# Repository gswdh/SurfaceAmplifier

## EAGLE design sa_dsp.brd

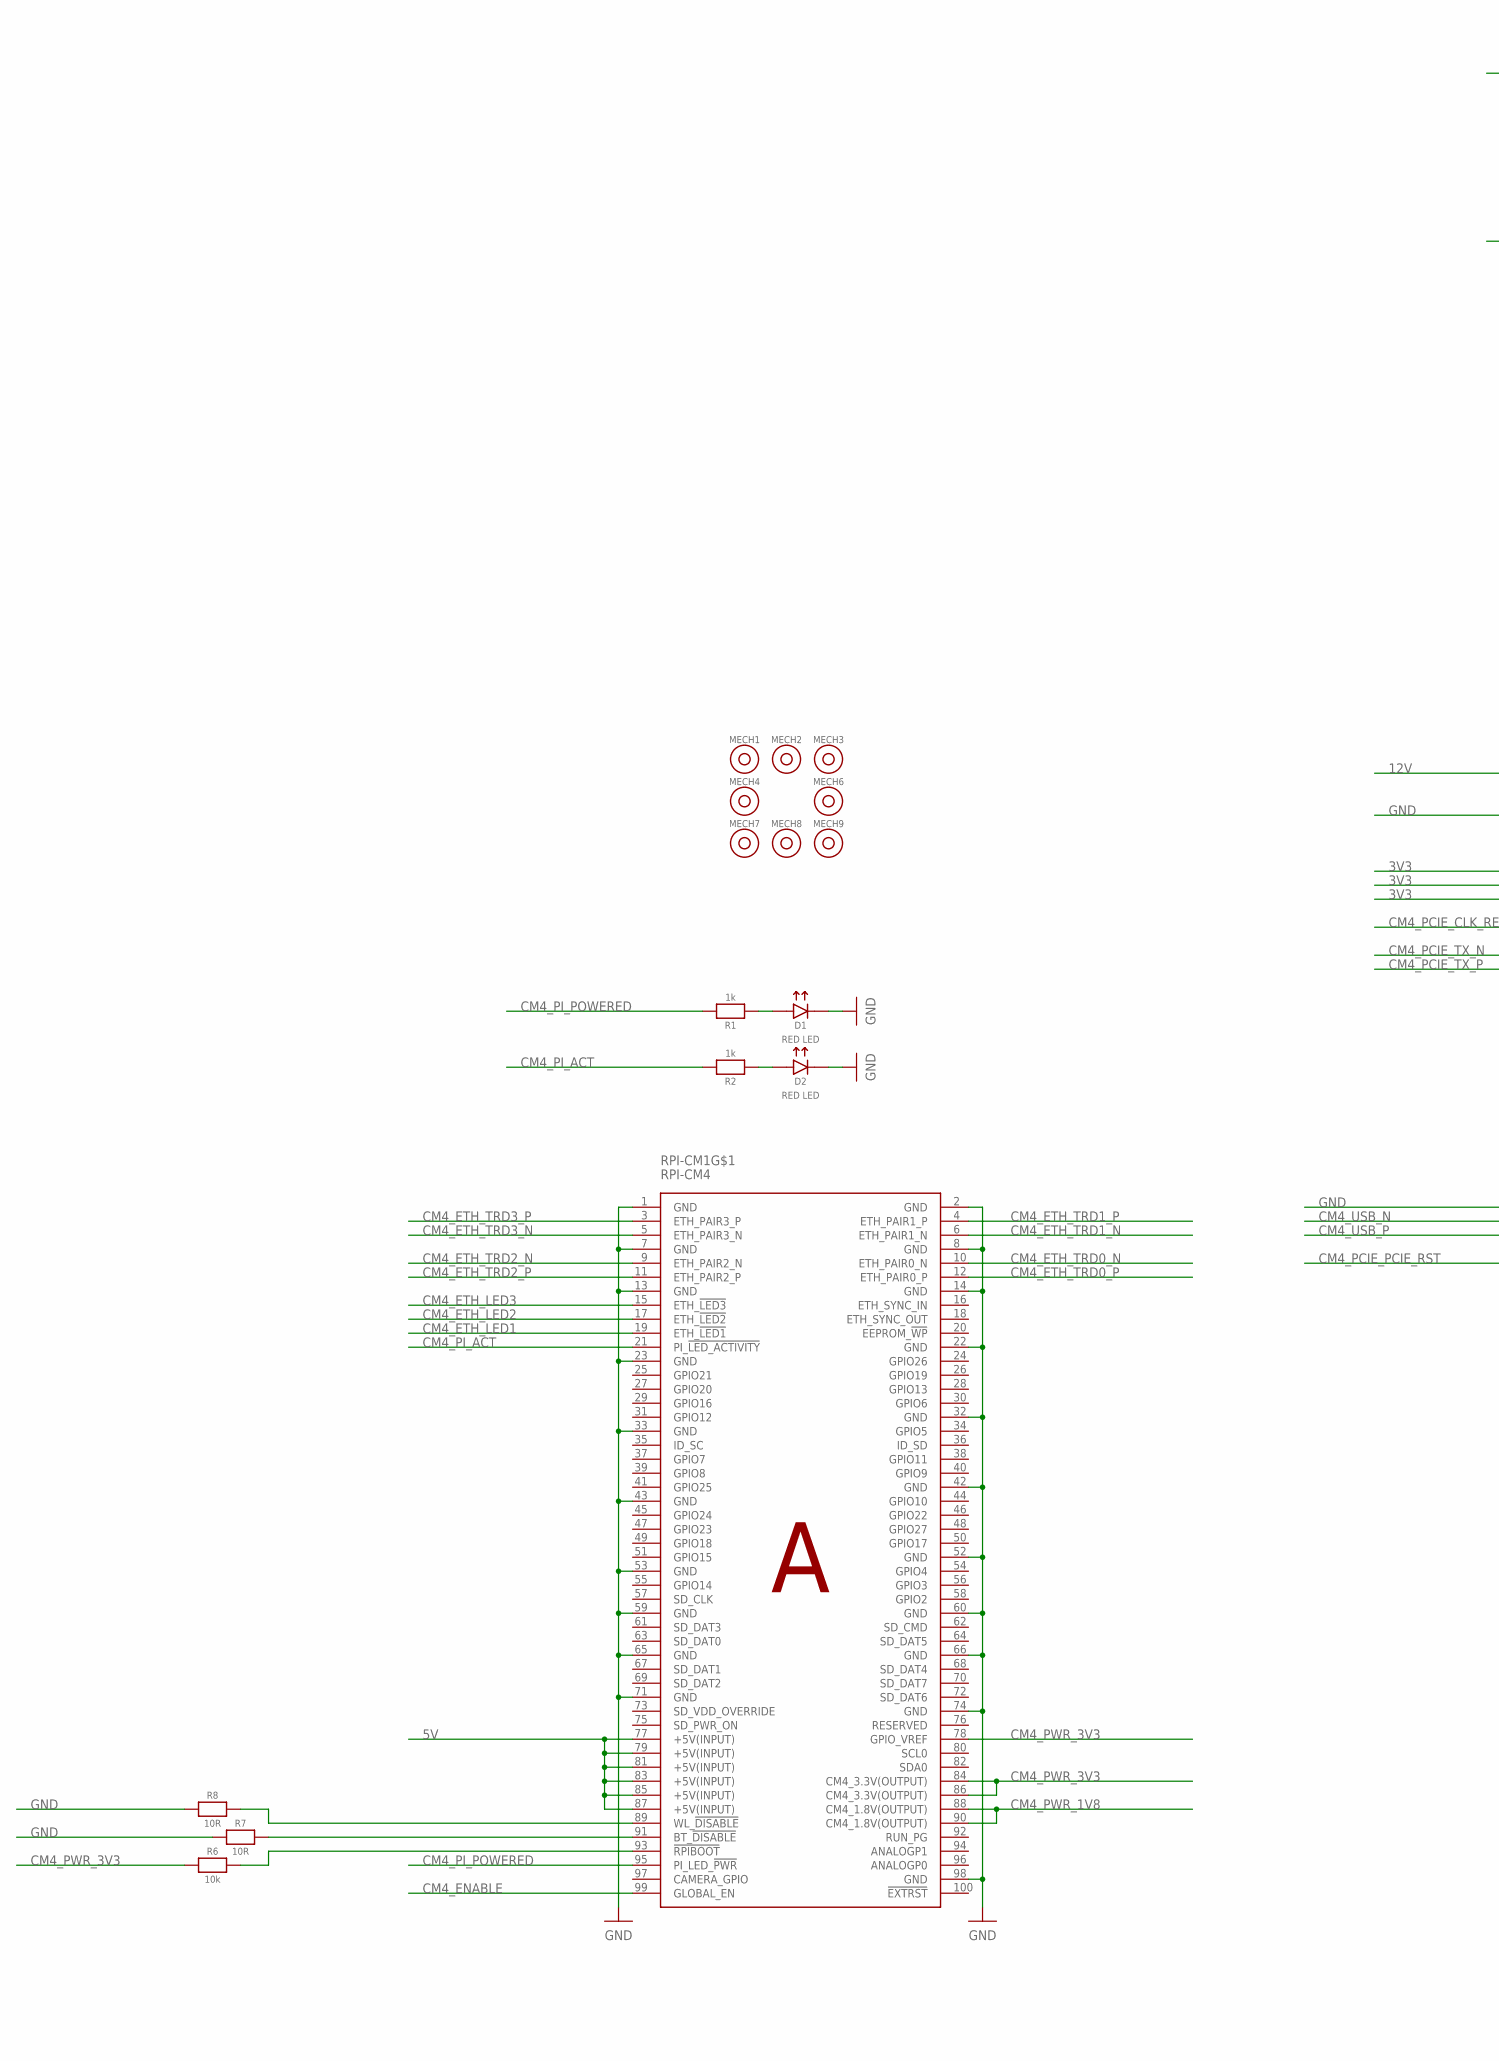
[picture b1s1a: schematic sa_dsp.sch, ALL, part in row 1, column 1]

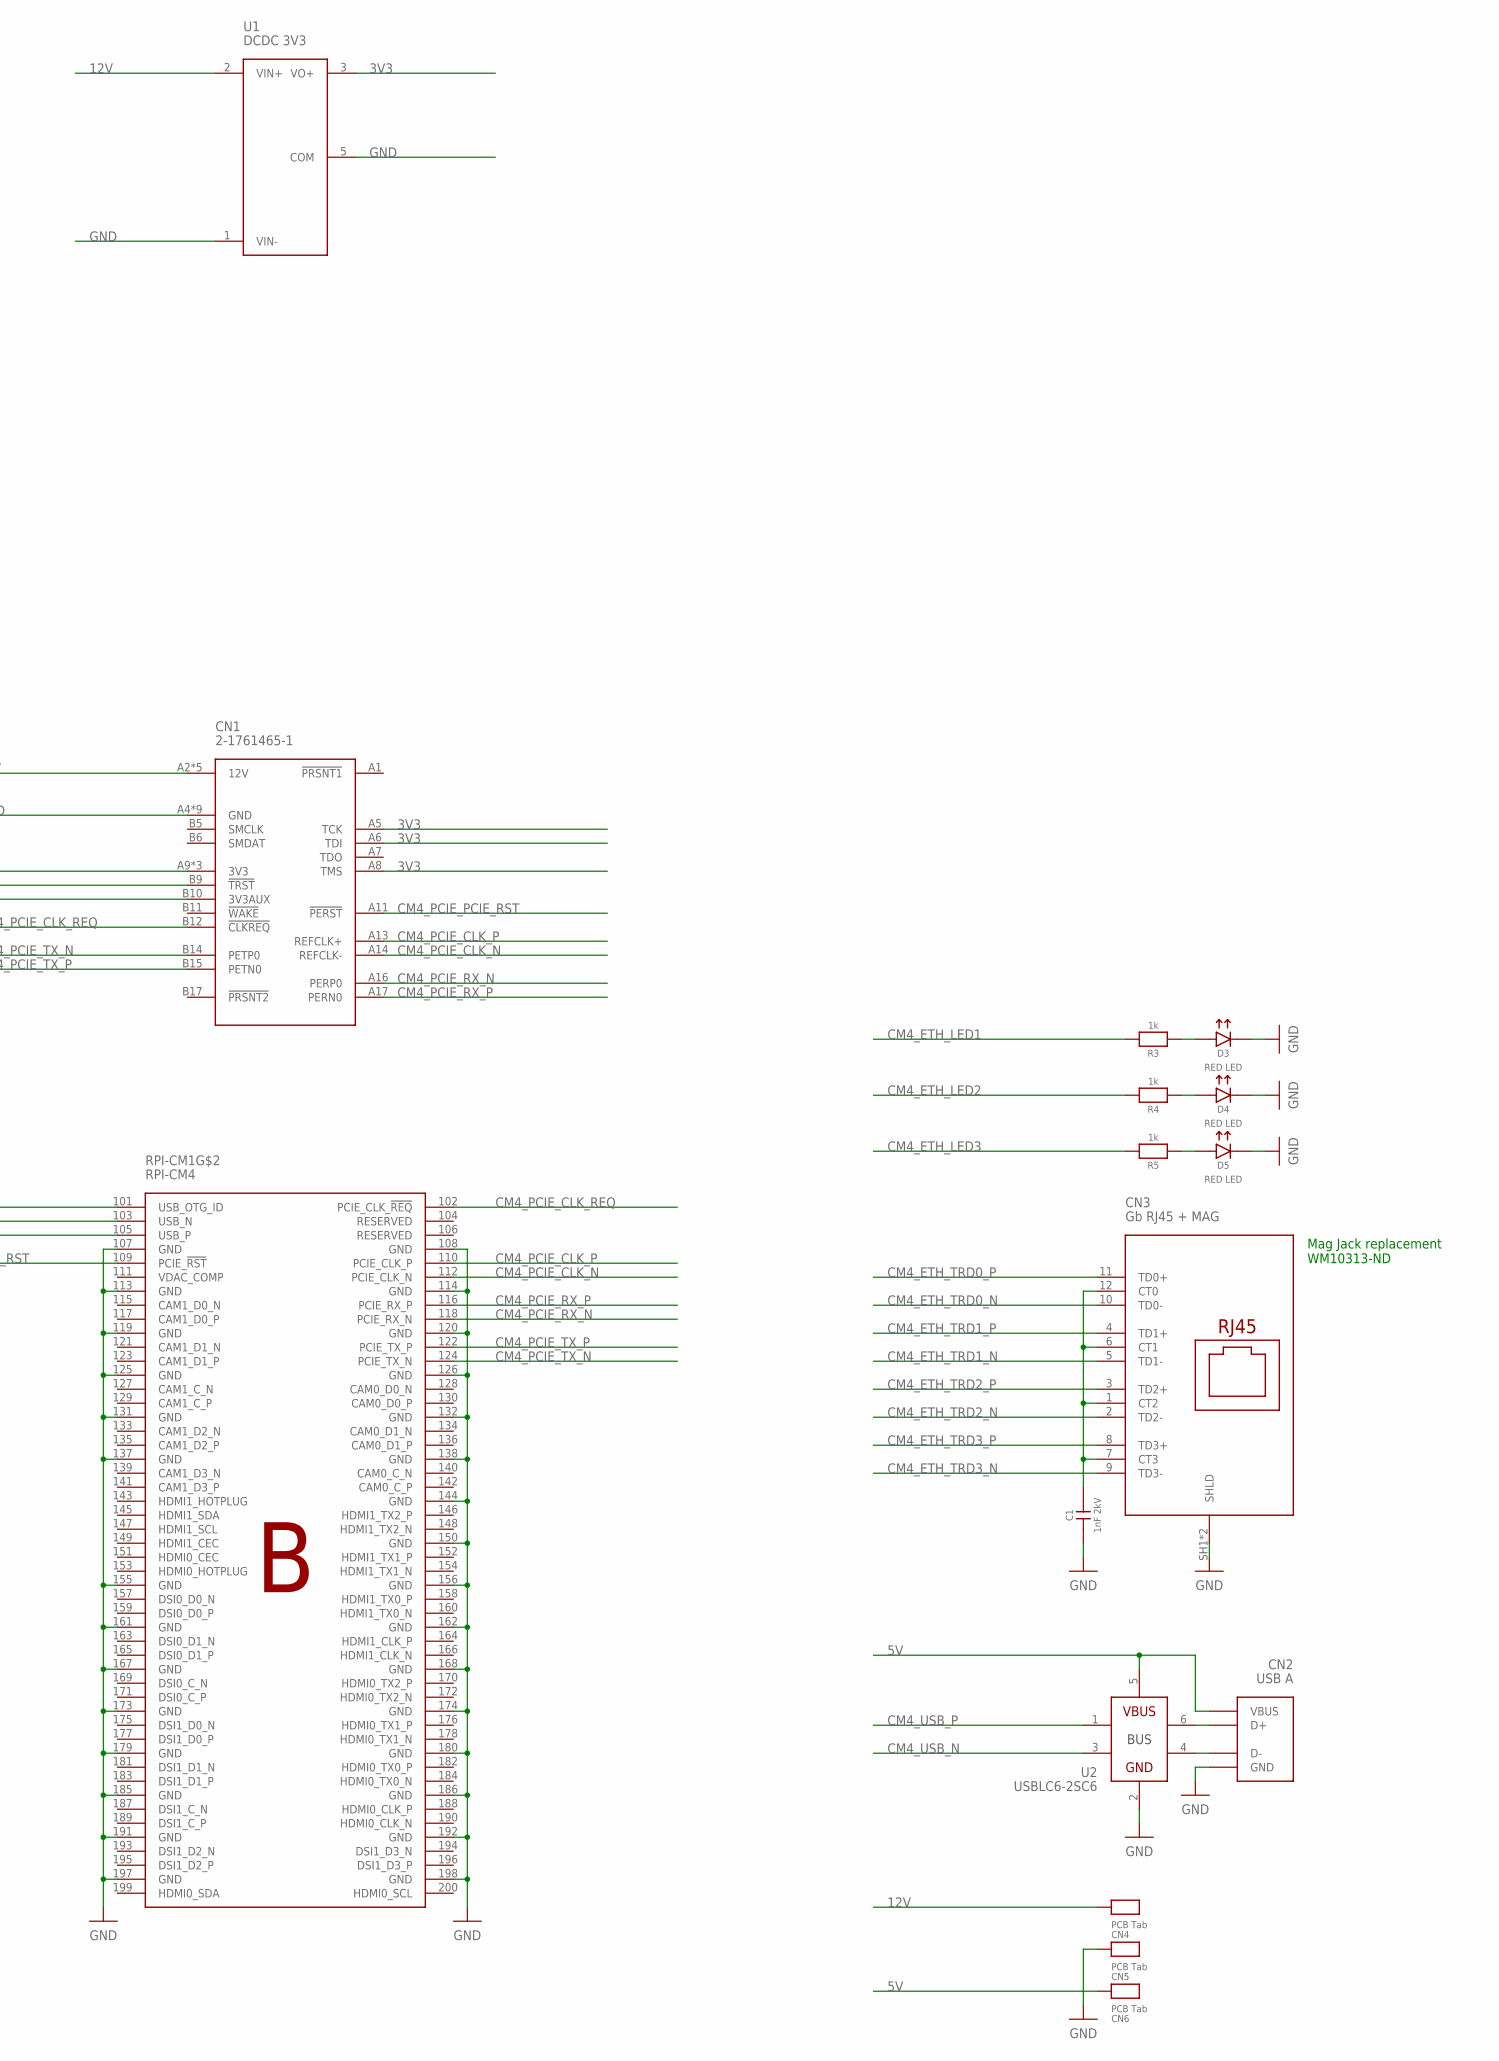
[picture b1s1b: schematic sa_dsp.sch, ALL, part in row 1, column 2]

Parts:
C1: 1nF 2kV; 1812
CN1: 2-1761465-1; CONN36_2-1761465-1_TEC
CN2: USB A; 629104190121
CN3: Gb RJ45 + MAG; 0857931020
CN4, CN5, CN6: PCB Tab; PCB_TAB_SMALL
D1, D2, D3, D4, D5: RED LED; 0603_POLAR
MECH1, MECH2, MECH3, MECH4, MECH6, MECH7, MECH8, MECH9: 6mm x 3mm; MOUNTHOLE_6X3
R1, R2, R3, R4, R5: 1k; 0603
R6: 10k; 0603
R7, R8: 10R; 0603
RPI-CM1: RPI-CM4
U1: DCDC 3V3; PDQE10
U2: USBLC6-2SC6; SOT23-6

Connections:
3V3: CN1.A5 (TCK), CN1.A6 (TDI), CN1.A8 (TMS), CN1.A9 (3V3), CN1.A10 (3V3), CN1.B8 (3V3), CN1.B9 (!TRST), CN1.B10 (3V3AUX), U1.3 (VO+)
5V: CN2.1 (VBUS), CN6.1, RPI-CM1.77 (+5V(INPUT)), RPI-CM1.79 (+5V(INPUT)), RPI-CM1.81 (+5V(INPUT)), RPI-CM1.83 (+5V(INPUT)), RPI-CM1.85 (+5V(INPUT)), RPI-CM1.87 (+5V(INPUT)), U2.5 (VBUS)
12V: CN1.A2 (12V), CN1.A3 (12V), CN1.B1 (12V), CN1.B2 (12V), CN1.B3 (12V), CN4.1, U1.2 (VIN+)
CM4_ENABLE: RPI-CM1.99 (GLOBAL_EN)
CM4_ETH_LED1: R3.2, RPI-CM1.19 (ETH_!LED1)
CM4_ETH_LED2: R4.2, RPI-CM1.17 (ETH_!LED2)
CM4_ETH_LED3: R5.2, RPI-CM1.15 (ETH_!LED3)
CM4_ETH_TRD0_N: CN3.10 (TD0-), RPI-CM1.10 (ETH_PAIR0_N)
CM4_ETH_TRD0_P: CN3.11 (TD0+), RPI-CM1.12 (ETH_PAIR0_P)
CM4_ETH_TRD1_N: CN3.5 (TD1-), RPI-CM1.6 (ETH_PAIR1_N)
CM4_ETH_TRD1_P: CN3.4 (TD1+), RPI-CM1.4 (ETH_PAIR1_P)
CM4_ETH_TRD2_N: CN3.2 (TD2-), RPI-CM1.9 (ETH_PAIR2_N)
CM4_ETH_TRD2_P: CN3.3 (TD2+), RPI-CM1.11 (ETH_PAIR2_P)
CM4_ETH_TRD3_N: CN3.9 (TD3-), RPI-CM1.5 (ETH_PAIR3_N)
CM4_ETH_TRD3_P: CN3.8 (TD3+), RPI-CM1.3 (ETH_PAIR3_P)
CM4_PCIE_CLK_N: CN1.A14 (REFCLK-), RPI-CM1.112 (PCIE_CLK_N)
CM4_PCIE_CLK_P: CN1.A13 (REFCLK+), RPI-CM1.110 (PCIE_CLK_P)
CM4_PCIE_CLK_REQ: CN1.B12 (!CLKREQ), RPI-CM1.102 (PCIE_CLK_!REQ)
CM4_PCIE_PCIE_RST: CN1.A11 (!PERST), RPI-CM1.109 (PCIE_!RST)
CM4_PCIE_RX_N: CN1.A16 (PERP0), RPI-CM1.118 (PCIE_RX_N)
CM4_PCIE_RX_P: CN1.A17 (PERN0), RPI-CM1.116 (PCIE_RX_P)
CM4_PCIE_TX_N: CN1.B14 (PETP0), RPI-CM1.124 (PCIE_TX_N)
CM4_PCIE_TX_P: CN1.B15 (PETN0), RPI-CM1.122 (PCIE_TX_P)
CM4_PI_ACT: R2.2, RPI-CM1.21 (PI_!LED_ACTIVITY)
CM4_PI_POWERED: R1.2, RPI-CM1.95 (PI_LED_!PWR)
CM4_PWR_1V8: RPI-CM1.88 (CM4_1.8V(OUTPUT)), RPI-CM1.90 (CM4_1.8V(OUTPUT))
CM4_PWR_3V3: R6.1, RPI-CM1.78 (GPIO_VREF), RPI-CM1.84 (CM4_3.3V(OUTPUT)), RPI-CM1.86 (CM4_3.3V(OUTPUT))
CM4_USB_N: RPI-CM1.103 (USB_N), U2.3 (D-_IN)
CM4_USB_P: RPI-CM1.105 (USB_P), U2.1 (D+_IN)
GND: C1.1, CN1.A4 (GND), CN1.A12 (GND), CN1.A15 (GND), CN1.A18 (GND), CN1.B4 (GND), CN1.B7 (GND), CN1.B13 (GND), CN1.B16 (GND), CN1.B18 (GND), CN2.4 (GND), CN2.SH1 (GND), CN2.SH2 (GND), CN2.SH3 (GND), CN2.SH4 (GND), CN3.SH1 (SHLD), CN3.SH2 (SHLD), CN5.1, D1.K, D2.K, D3.K, D4.K, D5.K, R7.1, R8.1, RPI-CM1.1 (GND), RPI-CM1.2 (GND), RPI-CM1.7 (GND), RPI-CM1.8 (GND), RPI-CM1.13 (GND), RPI-CM1.14 (GND), RPI-CM1.22 (GND), RPI-CM1.23 (GND), RPI-CM1.32 (GND), RPI-CM1.33 (GND), RPI-CM1.42 (GND), RPI-CM1.43 (GND), RPI-CM1.52 (GND), RPI-CM1.53 (GND), RPI-CM1.59 (GND), RPI-CM1.60 (GND), RPI-CM1.65 (GND), RPI-CM1.66 (GND), RPI-CM1.71 (GND), RPI-CM1.74 (GND), RPI-CM1.98 (GND), RPI-CM1.101 (USB_OTG_ID), RPI-CM1.107 (GND), RPI-CM1.108 (GND), RPI-CM1.113 (GND), RPI-CM1.114 (GND), RPI-CM1.119 (GND), RPI-CM1.120 (GND), RPI-CM1.125 (GND), RPI-CM1.126 (GND), RPI-CM1.131 (GND), RPI-CM1.132 (GND), RPI-CM1.137 (GND), RPI-CM1.138 (GND), RPI-CM1.144 (GND), RPI-CM1.150 (GND), RPI-CM1.155 (GND), RPI-CM1.156 (GND), RPI-CM1.161 (GND), RPI-CM1.162 (GND), RPI-CM1.167 (GND), RPI-CM1.168 (GND), RPI-CM1.173 (GND), RPI-CM1.174 (GND), RPI-CM1.179 (GND), RPI-CM1.180 (GND), RPI-CM1.185 (GND), RPI-CM1.186 (GND), RPI-CM1.191 (GND), RPI-CM1.192 (GND), RPI-CM1.197 (GND), RPI-CM1.198 (GND), U1.1 (VIN-), U1.5 (COM), U2.2 (GND)
unnamed: D1.A, R1.1
unnamed: CN2.2 (D-), U2.4 (D-OUT)
unnamed: D2.A, R2.1
unnamed: CN2.3 (D+), U2.6 (D+_OUT)
unnamed: D3.A, R3.1
unnamed: C1.2, CN3.1 (CT2), CN3.6 (CT1), CN3.7 (CT3), CN3.12 (CT0)
unnamed: D4.A, R4.1
unnamed: R6.2, RPI-CM1.93 (!RPIBOOT)
unnamed: D5.A, R5.1
unnamed: R7.2, RPI-CM1.91 (BT_!DISABLE)
unnamed: R8.2, RPI-CM1.89 (WL_!DISABLE)

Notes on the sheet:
Mag Jack replacement WM10313-ND

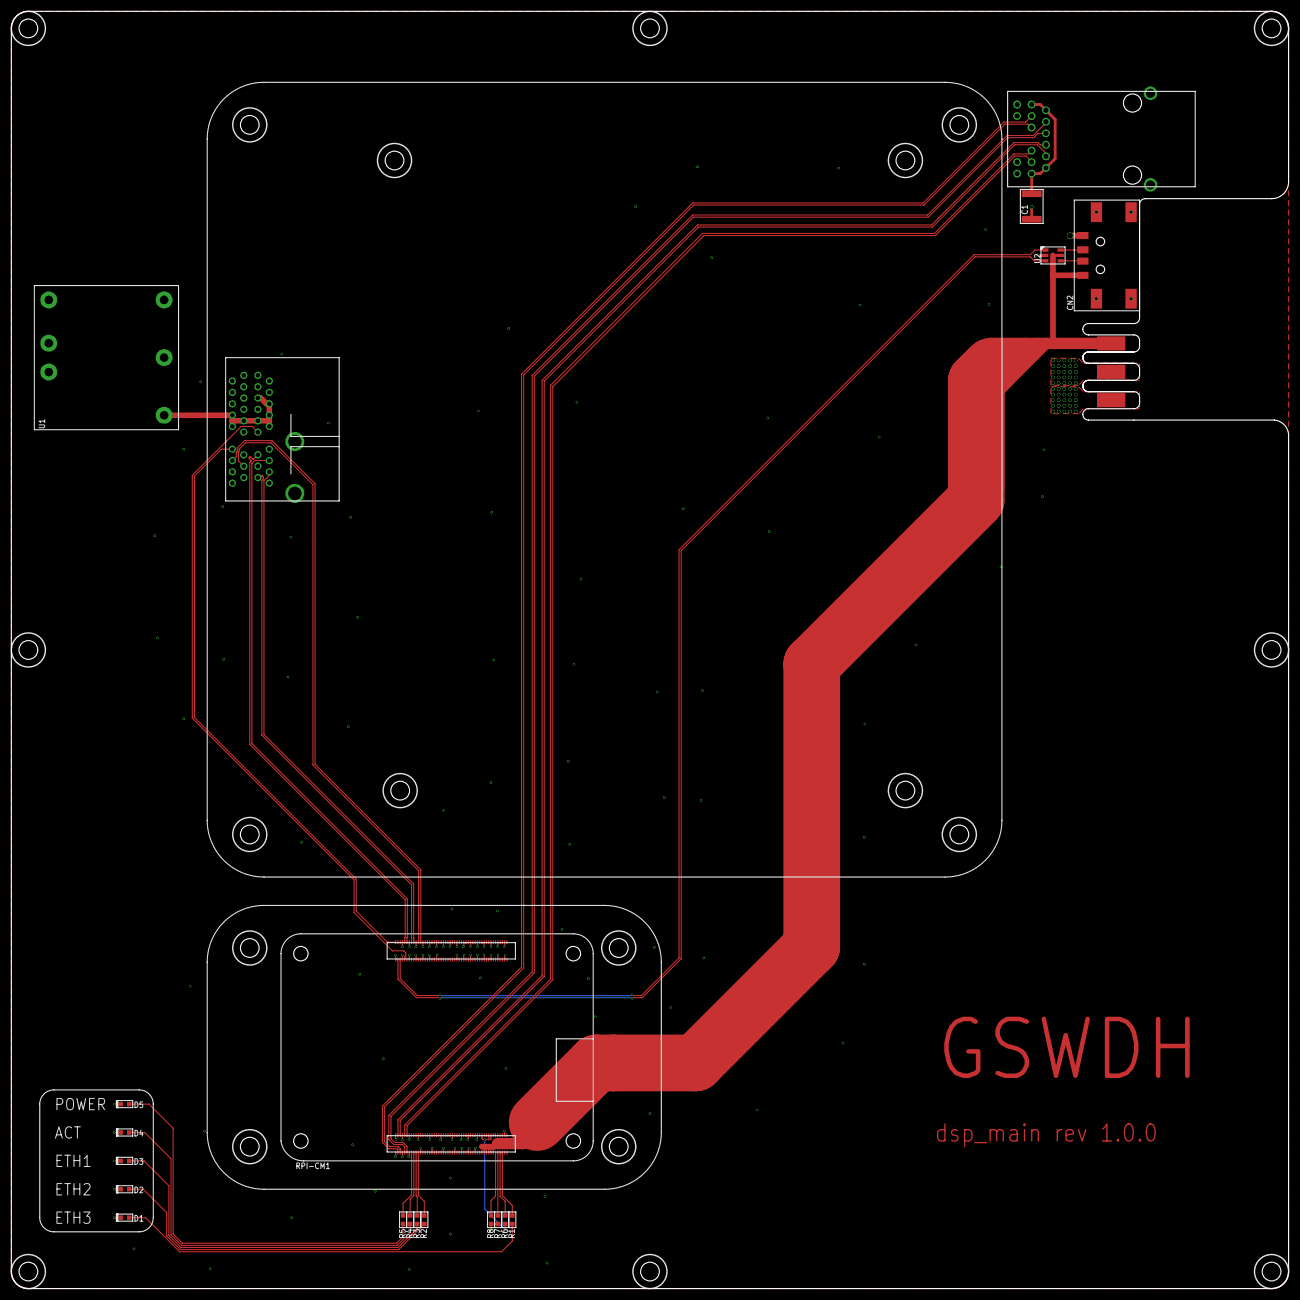
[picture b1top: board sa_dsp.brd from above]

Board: 4 copper layers, 225.0 x 225.0 mm, 43 parts (0 on the bottom side), 40 nets.

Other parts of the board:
MECH5, MECH10, MECH11, MECH12, MECH13, MECH14, MECH15, MECH16, MECH17, MECH18, MECH19, MECH20: 6mm x 3mm; MOUNTHOLE_6X3

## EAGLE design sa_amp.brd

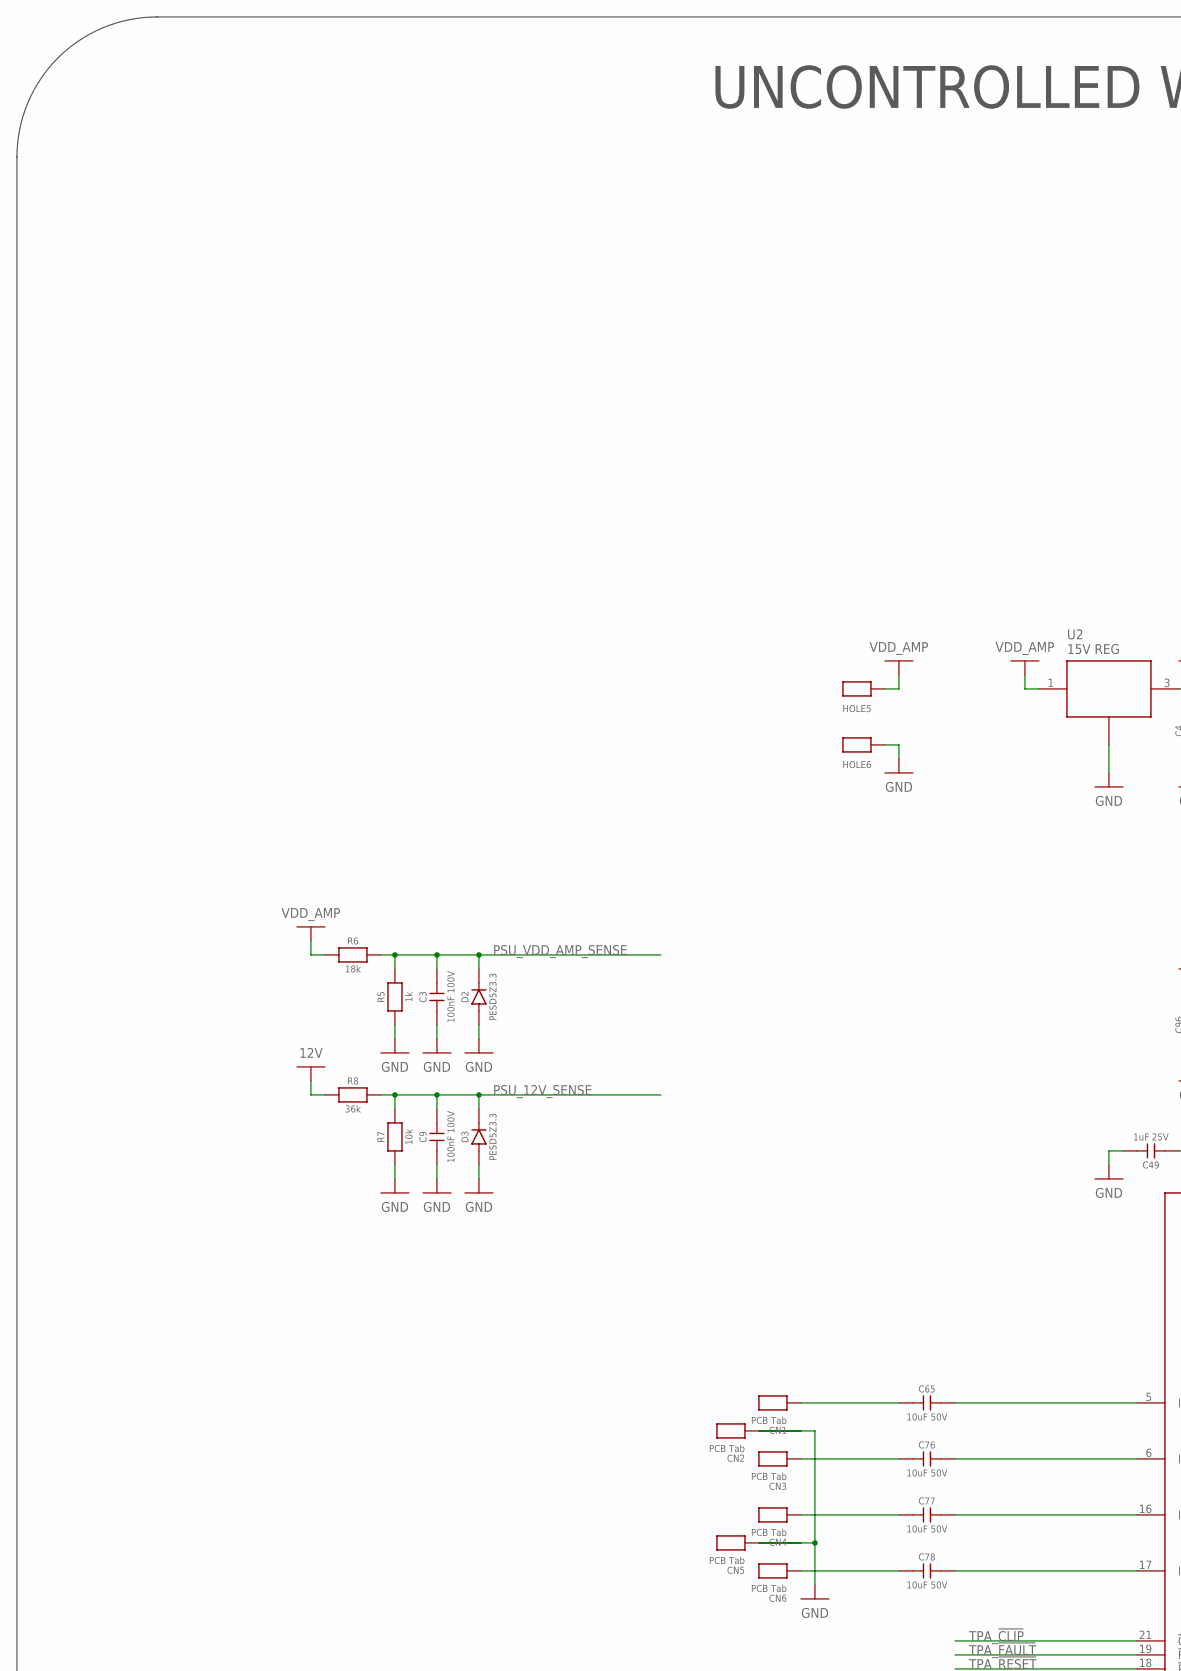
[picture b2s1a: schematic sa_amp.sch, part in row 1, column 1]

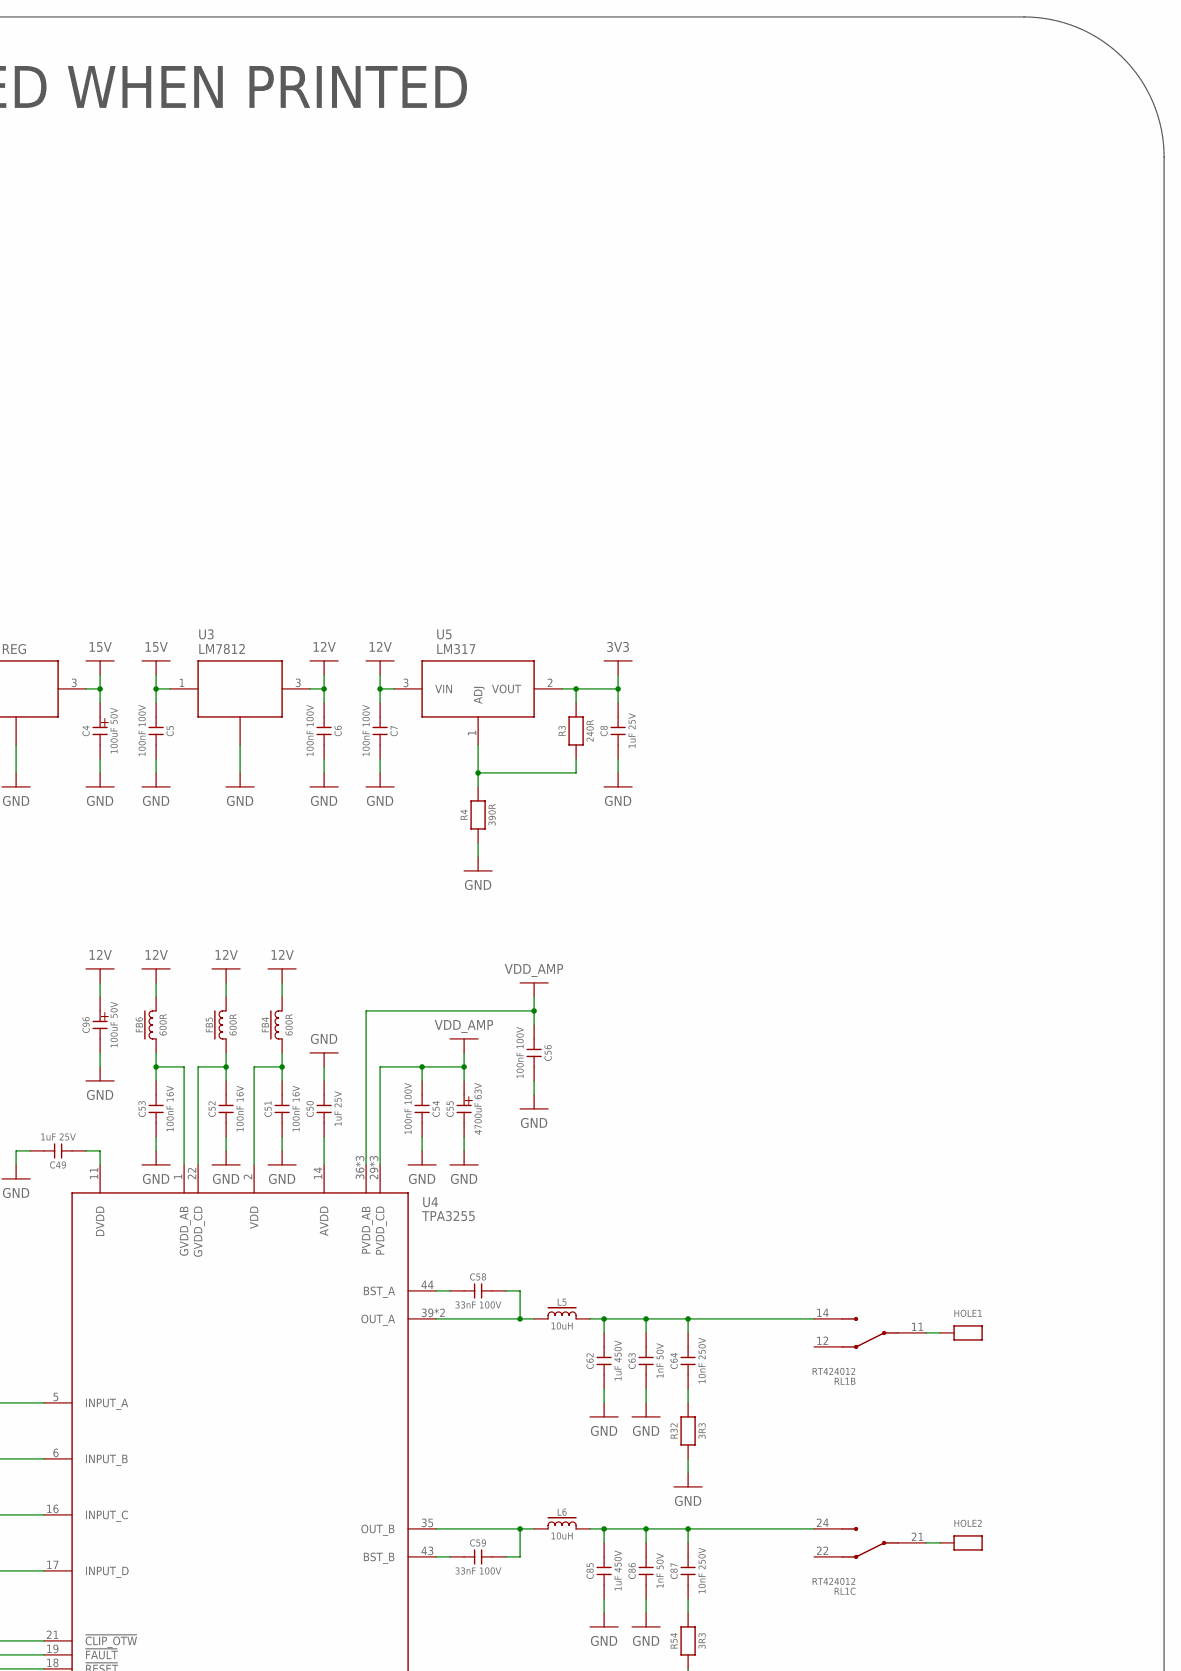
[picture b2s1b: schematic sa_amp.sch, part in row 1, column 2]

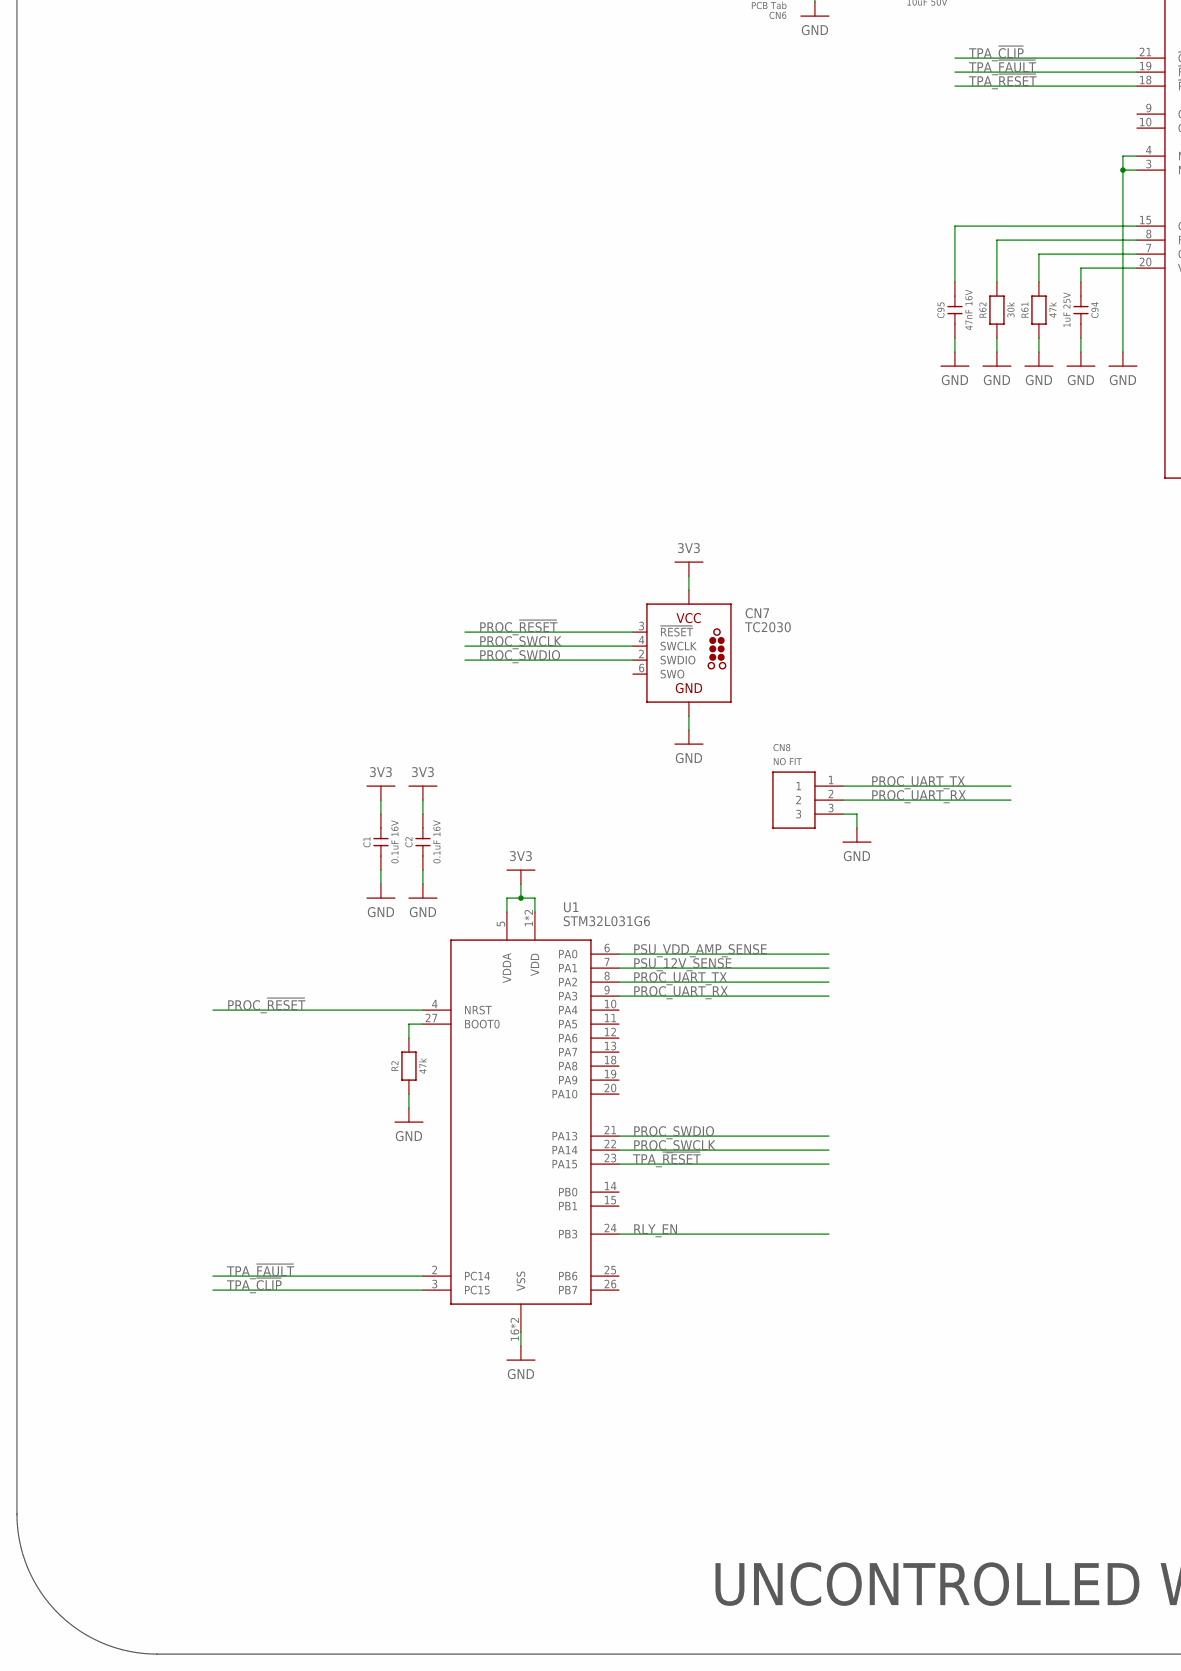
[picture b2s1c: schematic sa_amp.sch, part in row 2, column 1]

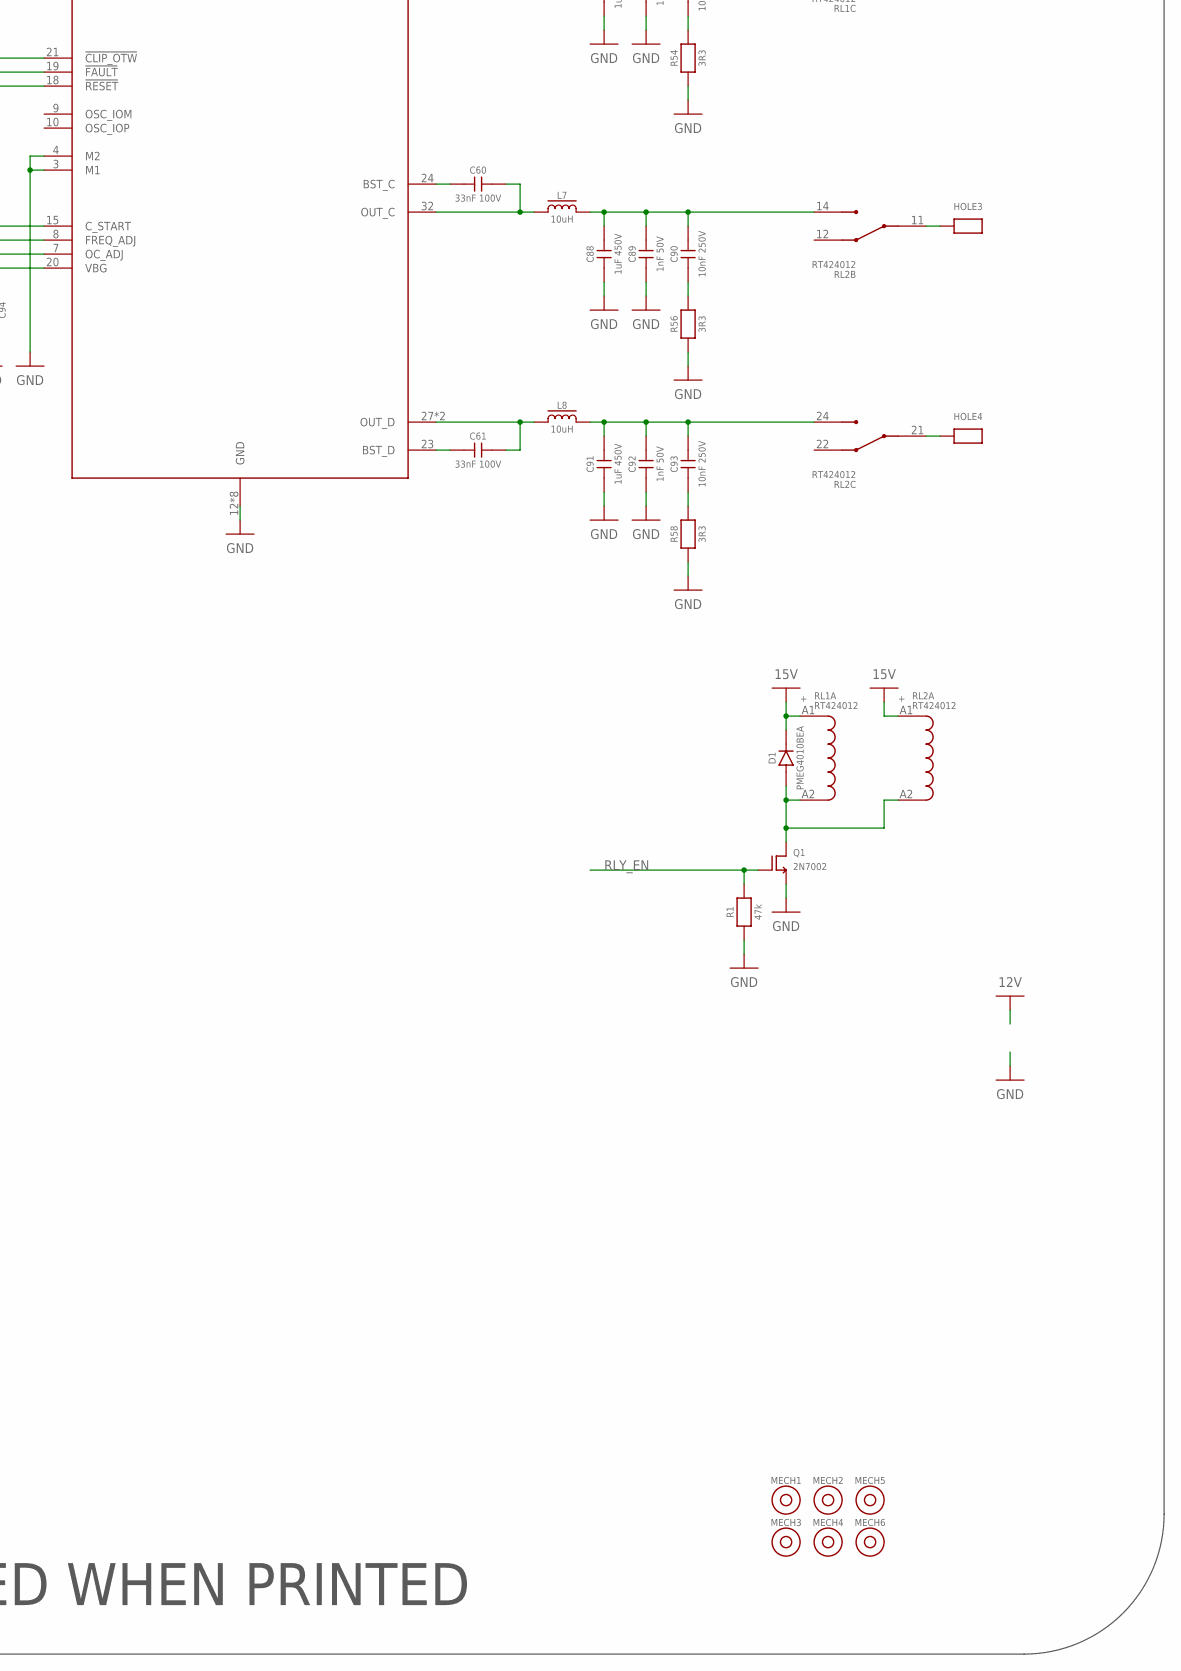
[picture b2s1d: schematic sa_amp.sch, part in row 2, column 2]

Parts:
C1, C2: 0.1uF 16V; 0603
C3, C5, C6, C7, C9, C54, C56: 100nF 100V; 0603
C4, C96: 100uF 50V; 8MM_RADIAL_3.5MM_PITCH
C8, C49, C50, C94: 1uF 25V; 0603
C51, C52, C53: 100nF 16V; 0603
C55: 4700uF 63V; 30MM_RADIAL_10MM_PITCH
C58, C59, C60, C61: 33nF 100V; 0603
C62, C85, C88, C91: 1uF 450V; 7X17.5BOX
C63, C86, C89, C92: 1nF 50V; 0603
C64, C87, C90, C93: 10nF 250V; 0603
C65, C76, C77, C78: 10uF 50V; 7.2X11BOX
C95: 47nF 16V; 0603
CN1, CN2, CN3, CN4, CN5, CN6: PCB Tab; PCB_TAB_SMALL
CN7: TC2030; TC2030-MCP
CN8: NO FIT; 3PIN_HEADER
D1: PMEG4010BEA; SOD-323
D2, D3: PESD5Z3.3; SC-79
FB4, FB5, FB6: 600R; 0603
HOLE1, HOLE2, HOLE3, HOLE4, HOLE5, HOLE6: PCB Tab; PCB_TAB
L5, L6, L7, L8: 10uH; SRP1265A
MECH1, MECH2, MECH3, MECH4, MECH5, MECH6: 6mm x 3mm; MOUNTHOLE_6X3
Q1: 2N7002; SOT23-3
R1, R2, R61: 47k; 0603
R3: 240R; 0603
R4: 390R; 0603
R5: 1k; 0603
R6: 18k; 0603
R7: 10k; 0603
R8: 36k; 0603
R32, R54, R56, R58: 3R3; 2512
R62: 30k; 0603
RL1, RL2: RT424012; 30MMDPDTRELAY
U1: STM32L031G6; UFQPN28
U2: 15V REG; SRH05
U3: LM7812; TO220
U4: TPA3255; HTSSOP44
U5: LM317; SOT89

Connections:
3V3: C1.2, C2.2, C8.2, CN7.1 (VCC), R3.2, U1.1 (VDD), U1.5 (VDDA), U1.17 (VDD), U5.2 (VOUT)
12V: C6.1, C7.1, C96.P (A), FB4.2, FB5.2, FB6.2, R8.1, U3.3 (VOUT), U5.3 (VIN)
15V: C4.P (A), C5.1, D1.K, RL1.A1, RL2.A1, U2.3 (VOUT), U3.1 (VIN)
GND: C1.1, C2.1, C3.2, C4.N (K), C5.2, C6.2, C7.2, C8.1, C9.2, C49.2, C50.2, C51.1, C52.1, C53.1, C54.2, C55.1 (K), C56.2, C62.1, C63.1, C85.1, C86.1, C88.1, C89.1, C91.1, C92.1, C94.2, C95.1, C96.N (K), CN2.1, CN5.1, CN7.5 (GND), CN8.3, D2.A, D3.A, HOLE6.1, Q1.3 (S), R1.1, R2.1, R4.1, R5.1, R7.1, R32.1, R54.1, R56.1, R58.1, R61.1, R62.1, U1.16 (VSS), U1.28 (VSS), U2.2 (GND), U3.2 (GND), U4.3 (M1), U4.4 (M2), U4.12 (GND), U4.13 (GND), U4.25 (GND), U4.26 (GND), U4.33 (GND), U4.34 (GND), U4.41 (GND), U4.42 (GND)
unnamed: C50.1, U4.14 (AVDD)
unnamed: C91.2, C92.2, C93.2, L8.2, RL2.24 (3)
unnamed: HOLE4.1, RL2.21 (1)
unnamed: HOLE1.1, RL1.11 (1)
unnamed: HOLE2.1, RL1.21 (1)
unnamed: HOLE3.1, RL2.11 (1)
unnamed: R2.2, U1.27 (BOOT0)
unnamed: D1.A, Q1.2 (D), RL1.A2, RL2.A2
unnamed: R3.1, R4.2, U5.1 (ADJ)
unnamed: C49.1, U4.11 (DVDD)
unnamed: C78.1, CN6.1
unnamed: C76.1, CN3.1
unnamed: C77.1, CN4.1
unnamed: C51.2, FB4.1, U4.2 (VDD)
unnamed: C52.2, FB5.1, U4.22 (GVDD_CD)
unnamed: C53.2, FB6.1, U4.1 (GVDD_AB)
unnamed: C61.1, U4.23 (BST_D)
unnamed: C61.2, L8.1, U4.27 (OUT_D), U4.28 (OUT_D)
unnamed: C60.1, U4.24 (BST_C)
unnamed: C60.2, L7.1, U4.32 (OUT_C)
unnamed: C59.1, U4.43 (BST_B)
unnamed: C59.2, L6.1, U4.35 (OUT_B)
unnamed: C58.1, U4.44 (BST_A)
unnamed: C58.2, L5.1, U4.39 (OUT_A), U4.40 (OUT_A)
unnamed: C64.1, R32.2
unnamed: C65.2, U4.5 (INPUT_A)
unnamed: C65.1, CN1.1
unnamed: C62.2, C63.2, C64.2, L5.2, RL1.14 (3)
unnamed: C76.2, U4.6 (INPUT_B)
unnamed: C77.2, U4.16 (INPUT_C)
unnamed: C78.2, U4.17 (INPUT_D)
unnamed: C85.2, C86.2, C87.2, L6.2, RL1.24 (3)
unnamed: C88.2, C89.2, C90.2, L7.2, RL2.14 (3)
unnamed: C87.1, R54.2
unnamed: C90.1, R56.2
unnamed: C93.1, R58.2
unnamed: C94.1, U4.20 (VBG)
unnamed: R61.2, U4.7 (OC_ADJ)
unnamed: R62.2, U4.8 (FREQ_ADJ)
unnamed: C95.2, U4.15 (C_START)
PROC_!RESET: CN7.3 (!RESET), U1.4 (NRST)
PROC_SWCLK: CN7.4 (SWCLK), U1.22 (PA14)
PROC_SWDIO: CN7.2 (SWDIO), U1.21 (PA13)
PROC_UART_RX: CN8.2, U1.9 (PA3)
PROC_UART_TX: CN8.1, U1.8 (PA2)
PSU_12V_SENSE: C9.1, D3.K, R7.2, R8.2, U1.7 (PA1)
PSU_VDD_AMP_SENSE: C3.1, D2.K, R5.2, R6.2, U1.6 (PA0)
RLY_EN: Q1.1 (G), R1.2, U1.24 (PB3)
TPA_!CLIP: U1.3 (PC15), U4.21 (!CLIP_OTW)
TPA_!FAULT: U1.2 (PC14), U4.19 (!FAULT)
TPA_!RESET: U1.23 (PA15), U4.18 (!RESET)
VDD_AMP: C54.1, C55.2 (A), C56.1, HOLE5.1, R6.1, U2.1 (VIN), U4.29 (PVDD_CD), U4.30 (PVDD_CD), U4.31 (PVDD_CD), U4.36 (PVDD_AB), U4.37 (PVDD_AB), U4.38 (PVDD_AB)

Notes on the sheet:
UNCONTROLLED WHEN PRINTED

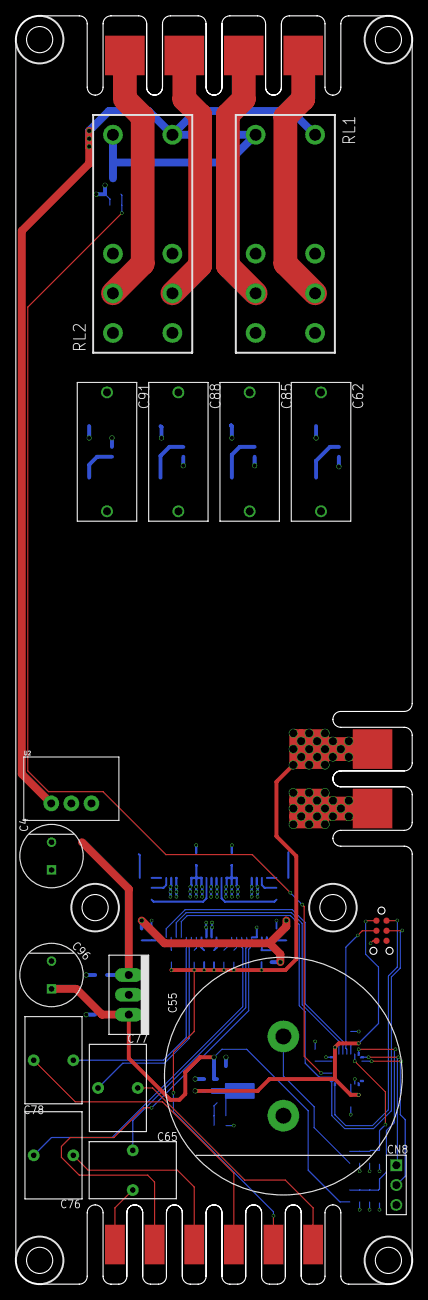
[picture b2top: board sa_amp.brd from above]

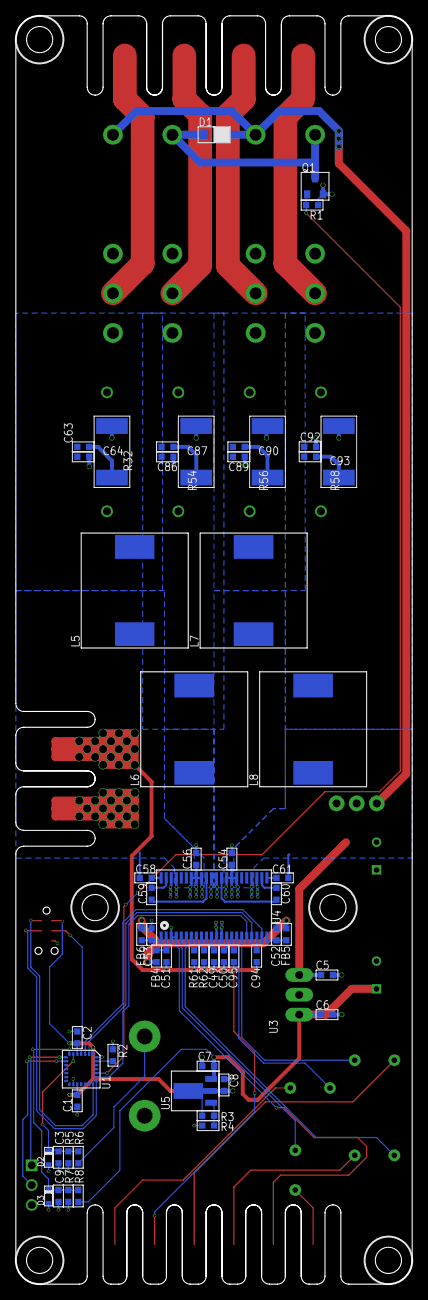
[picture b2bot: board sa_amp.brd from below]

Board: 4 copper layers, 50.0 x 160.0 mm, 92 parts (57 on the bottom side), 56 nets.

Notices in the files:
parts and their libraries:
tag-connect: ©2009 ROFA.cz - modified and updated by Robert Darlington ‹rdarlington@gmail.com›
